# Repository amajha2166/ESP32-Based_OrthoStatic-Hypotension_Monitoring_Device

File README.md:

# ESP32-Based Orthostatic Response and Vital Monitoring System

An embedded physiological monitoring prototype integrating **ESP32, MAX30102, MPU6050, Qt/QML, Wi-Fi communication, FreeRTOS-based notification handling, and KiCad hardware design**.

The project combines heart-rate and SpO₂ estimation, posture classification, resting-baseline acquisition, standing-response monitoring, and event-based alerts in a connected monitoring platform.

> **Project status:** Prototype under development. USB-powered operation has been demonstrated. Battery-powered operation requires further validation.

---

## Overview

The ESP32-Based Orthostatic Response and Vital Monitoring System is designed to demonstrate how embedded electronics, physiological sensors, real-time processing, and desktop visualization can be combined into a connected monitoring prototype.

The ESP32 acquires sensor data from the MAX30102 and MPU6050, processes the readings, manages the monitoring state machine, and transmits structured JSON messages over Wi-Fi TCP to a Qt-based graphical interface.

The system also supports user-triggered dizziness reporting and configurable notifications through the ntfy service.

The hardware design documentation includes the circuit architecture, component connections, and KiCad design files as they become available.

## Key Features

- **Heart-rate monitoring:** Estimates heart rate from MAX30102 optical pulse signals.
- **SpO₂ estimation:** Processes red and infrared sensor data to estimate blood oxygen saturation.
- **Posture classification:** Uses MPU6050 acceleration measurements and calibration-based posture references.
- **Resting baseline acquisition:** Collects valid heart-rate samples during a configured resting period.
- **Standing-response monitoring:** Observes heart-rate changes during a three-minute standing test.
- **Configurable response alerts:** Detects a sustained heart-rate increase relative to the resting baseline.
- **Qt/QML dashboard:** Displays sensor readings, posture, monitoring state, and alerts.
- **Wi-Fi TCP communication:** Transfers JSON-formatted data between the ESP32 and the Qt application.
- **Dizziness-event reporting:** Supports user-triggered events through available input methods.
- **Remote notifications:** Integrates with ntfy for notification delivery when network connectivity is available.
- **Battery-powered operation:** Includes a TP4056 charging module and MT3608 boost converter; the power system requires further validation.
- **KiCad hardware design:** Provides a place for schematic, PCB, and component documentation.

---

## System Architecture

```text
              MAX30102
          Heart Rate / SpO₂
                  |
                  | I²C
                  |
                  v
             +---------+
             |         |
             |  ESP32  | <----- MPU6050
             | DevKit  |        Acceleration /
             |         |        Posture Data
             +---------+
                  |
          Sensor Processing
          Posture Classification
          Monitoring State Machine
                  |
          +-------+--------+
          |                |
          v                v
     Wi-Fi TCP         Notification
     JSON Messages     Processing Task
          |                |
          v                v
      Qt/QML GUI       ntfy Service
          |
          v
   Monitoring Display
   and Event Reporting
```

## Hardware Components

| Component | Purpose |
|---|---|
| ESP32 DevKit V1 | Main microcontroller and Wi-Fi communication |
| MAX30102 | Optical heart-rate and SpO₂ sensing |
| MPU6050 | Accelerometer and gyroscope for posture-related measurements |
| TP4056 module | Single-cell lithium battery charging |
| 3.7 V, 400 mAh battery | Portable power source |
| MT3608 boost converter | Steps battery voltage up to a regulated output |
| LEDs and resistors | Visual status indicators |
| Active buzzer | Audible event indication, when installed and integrated |
| Computer | Qt dashboard, firmware development, and testing |

Component specifications and wiring must be checked against the actual hardware modules used.

## Software and Technologies

| Technology | Application |
|---|---|
| C/C++ | ESP32 firmware |
| Arduino framework | Firmware development |
| ESP32 Arduino Core | Microcontroller support |
| MAX3010x sensor library | MAX30102 interface |
| I²C | Sensor communication |
| FreeRTOS | Task-based embedded processing |
| Wi-Fi TCP | ESP32-to-Qt communication |
| JSON | Structured sensor data |
| Qt/QML | Desktop graphical interface |
| Qt Network | TCP client communication |
| HTTPS | Remote notification requests |
| ntfy | Notification delivery |
| KiCad | Electronic schematic and PCB design |

---

## Hardware Connections

### MAX30102

| MAX30102 | ESP32 DevKit V1 |
|---|---|
| SDA | GPIO 21 |
| SCL | GPIO 22 |
| GND | GND |
| VIN | Compatible supply for the sensor breakout |

### MPU6050

| MPU6050 | ESP32 DevKit V1 |
|---|---|
| SDA | GPIO 21 |
| SCL | GPIO 22 |
| GND | GND |
| VCC | Supply supported by the breakout board |

Both sensors share the I²C bus.

The firmware uses the following expected I²C addresses:

- MAX30102: `0x57`
- MPU6050: `0x68` or `0x69`

### Additional Indicators

The following GPIO assignments are used for the optional hardware additions:

| Component | ESP32 GPIO |
|---|---|
| Active buzzer | GPIO 25 |
| Battery-low LED | GPIO 26 |
| Vital-state LED | GPIO 27 |
| Battery-voltage sensing | GPIO 34 |

LEDs require appropriate current-limiting resistors. A buzzer that exceeds the safe GPIO current capability must use a suitable driver.

Battery-voltage sensing requires a correctly dimensioned voltage divider and appropriate ADC calibration.

### Battery Power Arrangement

The intended power path is:

```text
3.7 V Rechargeable Battery
            |
            v
       TP4056 Module
      B+ / B- terminals
            |
            v
      OUT+ / OUT-
            |
            v
     MT3608 Boost Converter
        IN+ / IN-
            |
            v
       Regulated 5 V
        OUT+ / OUT-
            |
            v
      ESP32 5V/VIN and GND
```

The MT3608 output must be measured and verified before connection to the ESP32.

The TP4056 board must be checked for battery protection and a suitable charging-current setting. The charger should not be assumed to provide regulated 5 V or automatic power-path management.

**Current power limitation:** The prototype has shut down during battery-powered operation after approximately two minutes, while USB-powered operation resumed normally. The cause has not yet been confirmed. Battery voltage, converter output under load, current demand, and protection behavior require investigation.

---

## Monitoring Workflow

### 1. Initialization

The ESP32 initializes the I²C bus and sensors, loads stored posture calibration values, and attempts to connect to Wi-Fi.

### 2. Physiological Measurement

The MAX30102 supplies optical pulse data used to estimate heart rate and SpO₂.

Measurement-validity flags help distinguish usable readings from invalid or unavailable measurements.

### 3. Posture Calibration

The MPU6050 provides acceleration data for calibration-based posture classification.

The firmware supports posture-calibration commands:

- `CAL_STAND`
- `CAL_SIT`
- `CAL_LIE`

Classification quality depends on sensor placement, calibration, and body movement.

### 4. Resting Baseline

The monitoring state machine begins in `WAIT_REST`.

A configured 30-second resting period is used to collect valid heart-rate samples. At least ten valid samples are required for a baseline to be accepted.

### 5. Standing Observation

After a valid baseline is obtained, the system enters `READY`.

When standing is detected, the system enters `TESTING` and starts a three-minute observation period.

The heart-rate difference is calculated as:

```text
Heart Rate Difference =
Current Heart Rate - Resting Baseline Heart Rate
```

The firmware uses a sustained increase of at least 30 BPM as its configured alert criterion.

This is an engineering threshold for the prototype and does not independently diagnose a medical condition.

### 6. Event Reporting

Dizziness can be reported using the supported button, serial, or Qt input mechanisms.

When configured and connected, the firmware can send event notifications through ntfy.

---

## Communication Protocol

The ESP32 provides a TCP server on port `8888` and transmits newline-delimited JSON messages approximately every 500 milliseconds.

The Qt application receives and parses these messages.

Example message structure:

```json
{
  "type": "vitals",
  "hr_bpm": 75.0,
  "spo2_pct": 98,
  "hr_valid": true,
  "spo2_valid": true,
  "posture": "SITTING",
  "mpu_ok": true,
  "max_ok": true,
  "ortho_state": "BASELINE",
  "ortho_flag": false
}
```

The values above are illustrative, not results from a recorded experiment. The actual JSON fields depend on the firmware version.

### Supported Commands

| Command | Function |
|---|---|
| `DIZZY` | Reports a dizziness event |
| `CAL_STAND` | Calibrates standing posture |
| `CAL_SIT` | Calibrates sitting posture |
| `CAL_LIE` | Calibrates lying posture |
| `RESET` | Resets the monitoring test |
| `SCAN` | Requests an I²C scan |
| `TEST_NOTIFY` | Tests notification delivery |

---

## Qt Dashboard

The Qt/QML dashboard provides a desktop interface for monitoring the system.

Its intended functions include:

- Displaying heart rate and SpO₂ estimates.
- Showing current posture.
- Displaying sensor initialization and validity status.
- Presenting the monitoring state and elapsed time.
- Showing the resting heart-rate baseline and current difference.
- Reporting dizziness events.
- Sending supported commands to the ESP32.

Add a screenshot of your actual Qt interface here.

```markdown

```

Replace the image path with your actual screenshot filename.

---

## KiCad Hardware Design

The repository's hardware section is intended to document the electronic design and its relationship to the assembled prototype.

Suggested contents:

```text
hardware/
├── kicad/
│   ├── project.kicad_pro
│   ├── project.kicad_sch
│   ├── project.kicad_pcb
│   └── README.md
├── wiring/
│   └── connections.md
└── BOM.md
```

### KiCad Deliverables

- **Schematic:** Electrical connections between the controller, sensors, power circuitry, and indicators.
- **PCB layout:** Component placement and routing, if a PCB has been designed.
- **Bill of Materials:** Component names, quantities, and relevant specifications.
- **Wiring documentation:** Connections used in the assembled prototype.
- **Design images:** Exported schematic or PCB screenshots for quick viewing on GitHub.

Include only the KiCad files that actually exist. If the prototype uses development boards connected by wires and no PCB has been designed, document the wiring diagram rather than claiming that a custom PCB is complete.

---

## Setup Instructions

### ESP32 Firmware

1. Install Arduino IDE and the ESP32 board support package.
2. Install the required MAX3010x library and any other dependencies used by the firmware.
3. Open the actual ESP32 `.ino` project.
4. Select the appropriate ESP32 DevKit V1 board configuration.
5. Configure Wi-Fi credentials and notification settings.
6. Connect the ESP32 over USB and upload the firmware.
7. Open Serial Monitor at `115200` baud.
8. Verify sensor initialization and calibration messages.

### Qt Application

1. Install a compatible Qt version and compiler toolchain.
2. Open the existing Qt project.
3. Configure the correct build kit.
4. Build and run the application.
5. Connect the application to the ESP32's configured IP address and TCP port.
6. Verify JSON reception and dashboard updates.

The exact Qt build instructions depend on the actual project files and Qt version.

### Posture Calibration

With the device mounted in its intended position, perform the calibration commands supported by the firmware.

Check each posture against the actual sensor placement and observe whether the classification remains stable during ordinary movement.

### Notification Configuration

Configure the ntfy topic and any required network settings in the firmware. Test notifications only with a valid configuration and internet connection.

Do not commit Wi-Fi passwords, private notification topics, tokens, or other secrets to GitHub.

---

## Testing and Validation

The following tests are used to evaluate the prototype:

| Test | Purpose |
|---|---|
| I²C detection | Verify sensor presence and communication |
| Heart-rate monitoring | Observe measurement availability and stability |
| SpO₂ estimation | Verify algorithm output and validity flags |
| Posture calibration | Check standing, sitting, and lying classifications |
| Baseline acquisition | Verify the resting interval and valid-sample requirements |
| Standing test | Verify test timing and state transitions |
| Alert processing | Check configured heart-rate response conditions |
| TCP communication | Verify JSON delivery to Qt |
| Event reporting | Test dizziness commands from supported inputs |
| Notifications | Verify ntfy delivery |
| Battery operation | Measure voltage stability and investigate shutdown |

Numerical accuracy and runtime should be reported only after they have been measured experimentally.

---

## Current Project Status

| Subsystem | Status |
|---|---|
| ESP32 firmware | Under development |
| MAX30102 integration | Implemented; measurement validation required |
| MPU6050 integration | Implemented; posture validation required |
| Resting-baseline state machine | Implemented in firmware |
| Standing observation logic | Implemented in firmware |
| Wi-Fi TCP/JSON communication | Implemented in firmware |
| Qt dashboard | Developed; verify against the current firmware protocol |
| Dizziness-event handling | Implemented in firmware; verify each input path |
| ntfy notifications | Integrated; delivery depends on configuration and connectivity |
| Battery power system | Requires further validation |
| KiCad documentation | Include available schematic and PCB design files |

---

## Limitations and Safety

- This is an educational and engineering prototype, not a clinically validated medical device.
- The system does not directly measure blood pressure and cannot diagnose orthostatic hypotension.
- Heart-rate and SpO₂ estimates may be affected by movement, sensor contact, perfusion, and signal quality.
- Posture classification depends on calibration and sensor placement.
- The baseline and alert thresholds are configured engineering parameters, not a substitute for clinical evaluation.
- Battery-powered operation requires additional electrical validation.
- The system should not be relied upon to prevent falls or provide emergency medical protection.

---

## Future Improvements

- Improve posture classification and transition detection.
- Add data logging and historical trend visualization.
- Improve Qt dashboard reliability and connection recovery.
- Add battery-voltage monitoring and runtime estimation.
- Validate converter stability and charging behavior.
- Improve sensor signal-quality checks.
- Conduct controlled comparisons against suitable reference devices.
- Complete and document the KiCad schematic and PCB design, if applicable.

---

## Technologies

`ESP32` · `C/C++` · `Arduino` · `MAX30102` · `MPU6050` · `I²C` · `FreeRTOS` · `Wi-Fi` · `TCP/IP` · `JSON` · `Qt` · `QML` · `KiCad` · `ntfy`

## License

Choose a license appropriate for your intended use and include the corresponding license file in the repository.

## Author

**[Your Name]**

Embedded Systems | Biomedical Monitoring | IoT | Hardware Design

GitHub: [Your GitHub Profile](https://github.com/)

Replace the author information and profile link before publishing.

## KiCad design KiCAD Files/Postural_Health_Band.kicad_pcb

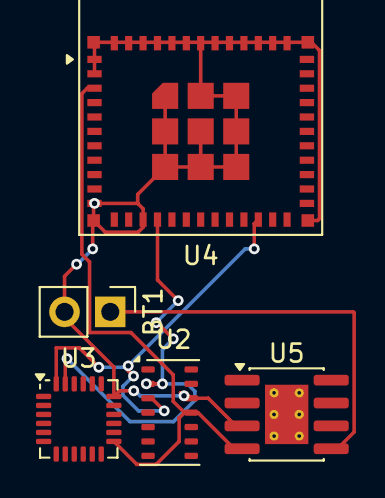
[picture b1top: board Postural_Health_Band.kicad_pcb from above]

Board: 2 copper layers, 5 parts (0 on the bottom side), 5 nets.

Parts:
BT1: Battery_Cell; PinHeader_1x02_P2.54mm_Vertical
U2: MAX30102; Maxim_OLGA-14_3.3x5.6mm_P0.8mm
U3: MPU-6050; InvenSense_QFN-24_4x4mm_P0.5mm
U4: ESP32-C6-MINI-1
U5: TP4056-42-ESOP8; SOIC-8-1EP_3.9x4.9mm_P1.27mm_EP2.41x3.3mm_ThermalVias

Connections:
unnamed: BT1.1 (+), U5.5 (BAT)
unnamed: BT1.2 (-), U2.12 (GND), U3.18 (GND), U4.1 (GND), U4.2 (GND), U4.11 (GND), U4.14 (GND), U4.36 (GND), U4.37 (GND), U4.38 (GND), U4.39 (GND), U4.40 (GND), U4.41 (GND), U4.42 (GND), U4.43 (GND), U4.44 (GND), U4.45 (GND), U4.46 (GND), U4.47 (GND), U4.48 (GND), U4.49 (GND), U4.50 (GND), U4.51 (GND), U4.52 (GND), U4.53 (GND), U5.3 (GND)
unnamed: U2.2 (SCL), U3.23 (SCL), U4.15 (IO6)
unnamed: U2.3 (SDA), U3.24 (SDA), U4.22 (IO8)
unnamed: U2.11 (VDD), U3.13 (VDD), U4.3 (3V3), U5.4 (V_{CC})
